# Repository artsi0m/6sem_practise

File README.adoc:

/// -*- mode: adoc; -*-
= PCB project of RS485 — RS232 converter from 6 semester practise in BSUIR =

|===
| Folder | Сontent

| kicad-rs-converter
| PCB project in KiCAD

| paper
| practise report

| SEL
| structured element list (Перечень элементов)
|===

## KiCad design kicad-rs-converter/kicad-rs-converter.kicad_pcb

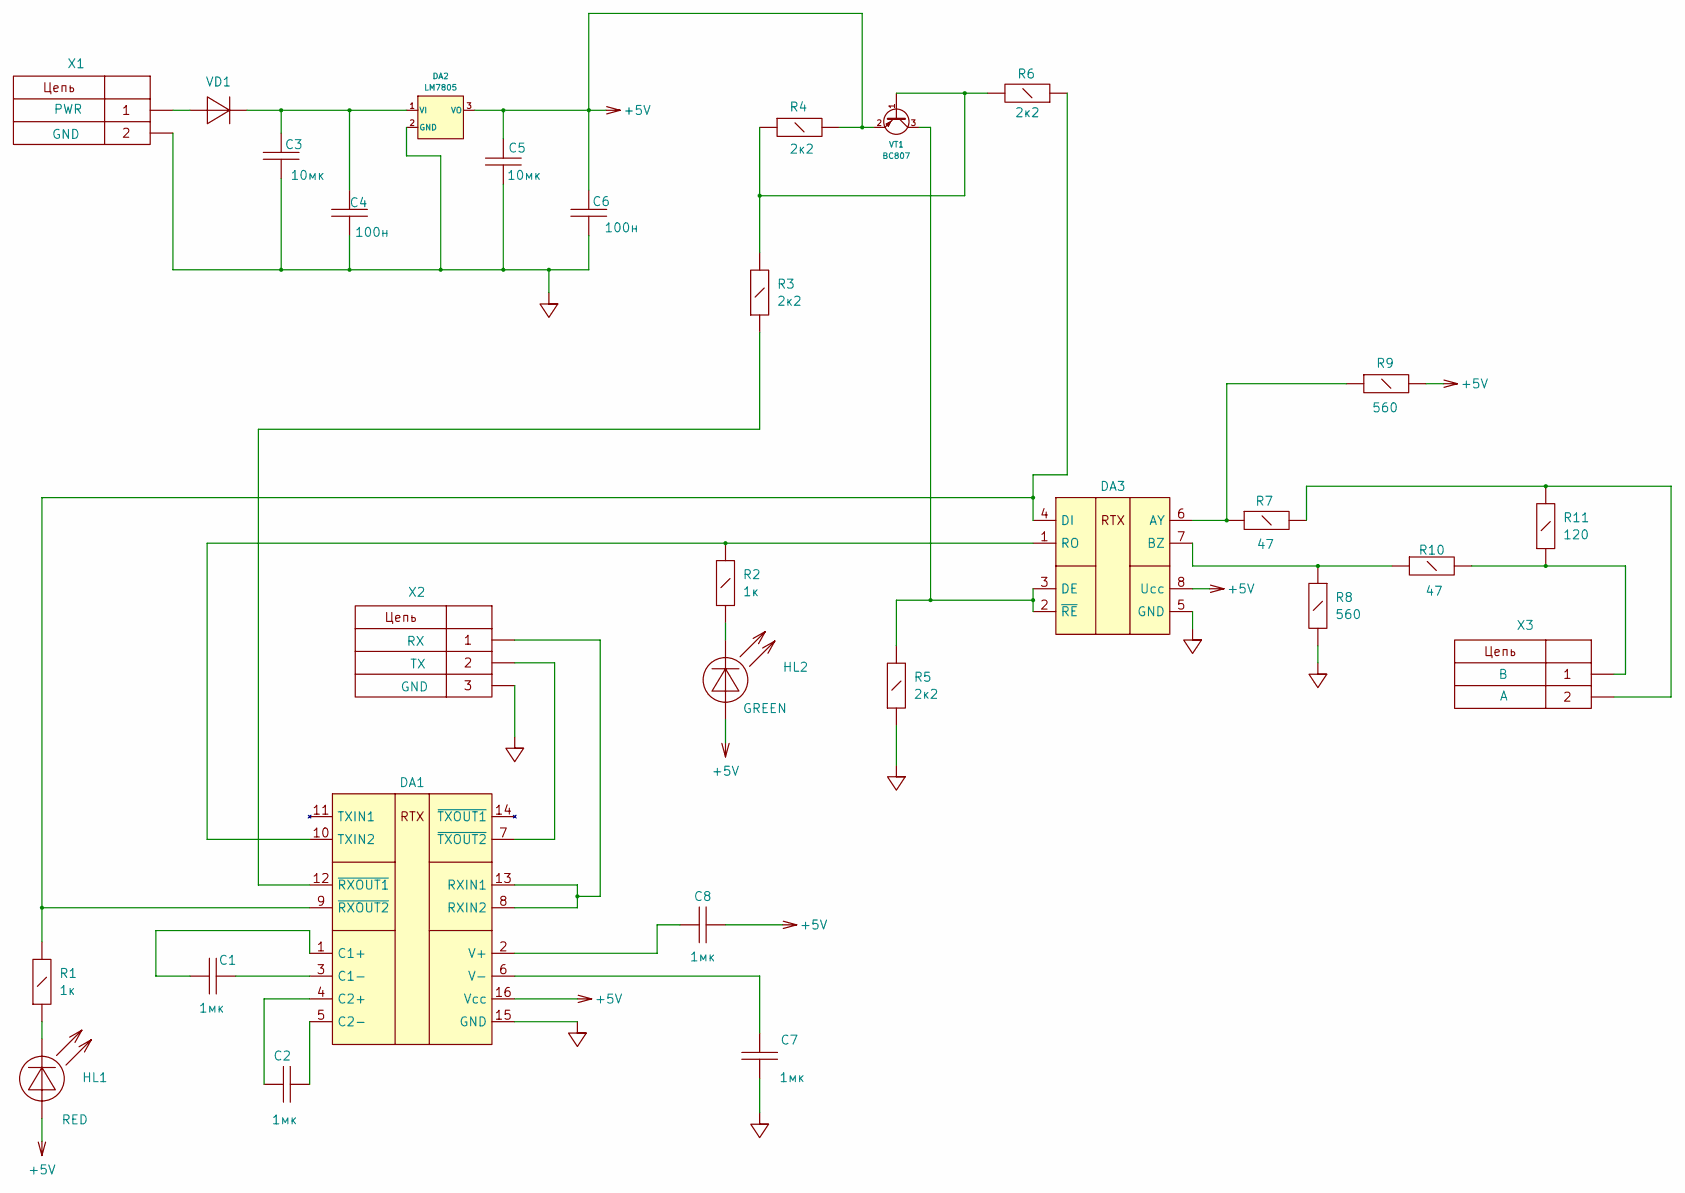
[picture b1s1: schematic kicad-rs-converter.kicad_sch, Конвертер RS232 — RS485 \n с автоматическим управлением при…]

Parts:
C1, C2, C7, C8: 1мк; C_1206_3216Metric
C3, C5: 10мк; C_1206_3216Metric
C4, C6: 100н; C_1206_3216Metric
DA1: MAX232_GOST; SO-16_3.9x9.9mm_P1.27mm
DA2: LM7805; TO-252-2
DA3: MAX485; SO-8_3.9x4.9mm_P1.27mm
HL1: RED; LED_1210_3225Metric
HL2: GREEN; LED_1210_3225Metric
R1, R2: 1к; R_0603_1608Metric
R3, R4, R5, R6: 2к2; R_0603_1608Metric
R7, R10: 47; R_0603_1608Metric
R8, R9: 560; R_0603_1608Metric
R11: 120; R_0603_1608Metric
VD1: VD; D_0805_2012Metric
VT1: BC807; SOT-23
X1: CONN_PWR; TerminalBlock_Phoenix_PT-1,5-2-5.0-H_1x02_P5.00mm_Horizontal
X2: CONN_RS232; TerminalBlock_Phoenix_PT-1,5-3-5.0-H_1x03_P5.00mm_Horizontal
X3: CONN_2; TerminalBlock_Phoenix_PT-1,5-2-5.0-H_1x02_P5.00mm_Horizontal

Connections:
+5V: C5.1, C6.1, C8.2, DA1.16 (Vcc), DA2.3 (VO), DA3.8 (Ucc), HL1.2 (A), HL2.2 (A), R4.2, R9.2, VT1.2 (E)
GND: C3.2, C4.2, C5.2, C6.2, C7.1, DA1.15 (GND), DA2.2 (GND), DA3.5 (GND), R5.1, R8.2, X1.2, X2.3
unnamed: C1.1, DA1.1 (C1+)
unnamed: C1.2, DA1.3 (C1-)
unnamed: C2.1, DA1.4 (C2+)
unnamed: C2.2, DA1.5 (C2-)
unnamed: DA1.8 (RXIN2), DA1.13 (RXIN1), X2.1
unnamed: DA1.10 (TXIN2), DA3.1 (RO), R2.2
unnamed: C8.1, DA1.2 (V+)
unnamed: C7.2, DA1.6 (V-)
unnamed: DA1.12 (~RXOUT1), R3.1
unnamed: DA1.9 (~RXOUT2), DA3.4 (DI), R1.2, R6.1
unnamed: DA1.7 (~TXOUT2), X2.2
unnamed: C3.1, C4.1, DA2.1 (VI), VD1.1 (K)
unnamed: DA3.6 (AY), R7.1, R9.1
unnamed: DA3.7 (BZ), R8.1, R10.1
unnamed: DA3.2 (~RE), DA3.3 (DE), R5.2, VT1.3 (C)
unnamed: HL1.1 (K), R1.1
unnamed: HL2.1 (K), R2.1
unnamed: R10.2, R11.1, X3.1
unnamed: R7.2, R11.2, X3.2
unnamed: VD1.2 (A), X1.1
unnamed: R3.2, R4.1, R6.2, VT1.1 (B)

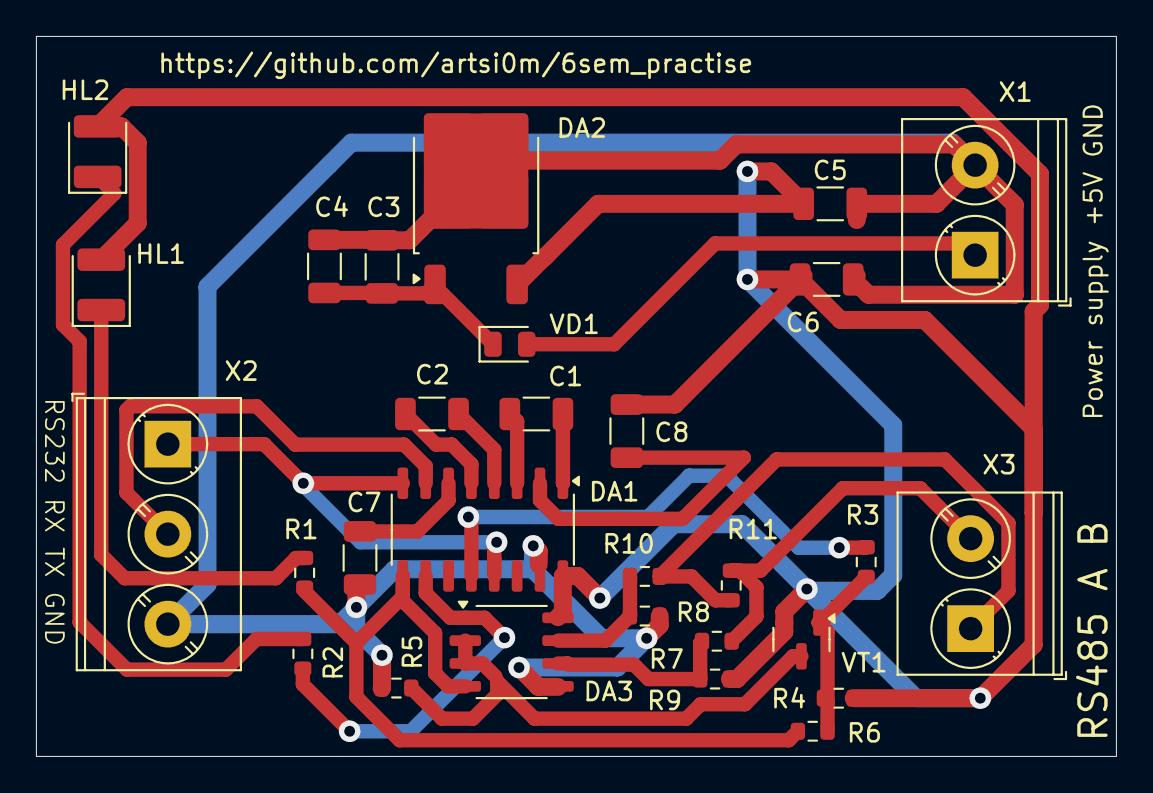
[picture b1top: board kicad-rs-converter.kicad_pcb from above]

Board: 2 copper layers, 60.0 x 40.0 mm, 29 parts (0 on the bottom side), 23 nets.

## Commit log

2024-06-11 Initiated with autogenerated gitignore file.
2024-06-11 Imported class file from 6 sem coursework repo
2024-06-11 Copied build script from repo of the coursework
2024-06-11 Excluding compilation result
2024-06-11 Added copied files from 6sem couserwork +test file + bibliography
2024-06-18 Initial commit with empty kicad project
2024-06-19 Рамка по ГОСТ
2024-06-19 Placed two XS's on scheme
2024-06-19 Created symbol library and copied MAX485CPA from GOST library
2024-06-19 Filter out kicad lock files with gitignore
2024-06-19 Filter out kicad lock files with .gitignore attempt 2
2024-06-19 Changed link to datasheet
2024-06-19 That symbol was already present in GOST library
2024-06-20 rewriting title.tex from coursework
2024-06-20 Placed MAX232 to the left as much as I could
2024-06-20 Part of the circuit with the second LED
2024-06-20 Created GOST symbol for LM7805
2024-06-20 Created part of circuit with voltage regulator
2024-06-20 Created part of circuit with MAX485 only
2024-06-20 Placed MAX485 on the scheme
2024-06-20 Schematics almost done, all parts of circuit is on the scheme
2024-06-20 Fixed scheme, pwr connector named, RXOUT2 of MAX484 connected
2024-06-20 Write down surnames
2024-06-20 Scheme annotation
2024-06-20 Placed values on every element
2024-06-20 s/LM7805_TO220_GOST/LM7805/
2024-06-20 MAX232 and MAX485 in my own library
2024-06-20 Fixing errors from ERC
2024-06-20 ERC fix with PWR_flag, PWR_CONN in sym_lib, package for MAX232 assigned
2024-06-20 BC327 to BC807 smd, SOT-23, set most of the scheme to smd.
2024-06-21 A4 to A3, because of the GOST norms for sheet
2024-06-21 Renamed designators of MAX485 and MAX232 to DA from DD
2024-06-21 Created separate connector symbol for RS232
2024-06-21 Schematic redone on A3
2024-06-21 Assigned values almost everywhere, writing sheet
2024-06-21 ESKD class assigned
2024-06-21 footprints for MAX232 & MAX485
2024-06-21 Placed footprints for LED
2024-06-21 Placed footprints for Resistors
2024-06-21 Placed footprints for polar capacitors
2024-06-21 Footprint for SMD Capacitors and Resistors
2024-06-24 Changed from polar CP capacitors to regular capacitors C
2024-06-24 Assigned footprint of SMD:C_1206_3216 Metric to every capacitor
2024-06-24 Assigned footprints for X connector — Terminal Block
2024-06-24 Imported footprints from schematics into PCB layout
2024-06-24 Assigned netclasses and colors for cicuits
2024-06-24 Drawing edge cuts
2024-06-24 PCBdoc: everything connected except for GND and +5V
2024-06-24 pcbdoc finished, but some parts can be done better.
2024-06-24 Made PCB layout on 70x40mm board
2024-06-24 Moved transistor BC807 and redone PCB layout a little bit.
2024-06-24 Rebuild from scratch. 0.8 track_width and 60x40mm board
2024-06-25 Exported bom
2024-06-25 Начал перечень писать
2024-06-25 More resistors
2024-06-25 README with kicad-rc-converter, paper, SEL folders mentioned
2024-06-25 quick fix to hide emacs mode directive
2024-06-25 README in org mode with 3 folders mentioned
2024-06-28 Silkscreen added on pcb
2024-06-28 Link to original schematic + formatted
2024-06-28 Full structured element list, but something with formatting
2024-07-01 Fixed DRC error from silkscreen plaeced near footprint
2024-07-01 Repaired document by removing \XeselEntry{}{}{}{} from first lines
2024-07-01 longer DocumentName, SEL seems to be fineshed
2024-07-06 There is an error, PWR_FLAG removed to see if fixing would fix ERC
2024-07-06 The fix consisted of flipping transistor
2024-07-07 trying to make place with error more readable
2024-07-07 transistor flip and reconnect on pcbdoc
2024-07-08 Fix the Surname of the one who checks the work
2024-09-02 Cannot build on openSUSE, no such font in fetchmsttfonts
2024-09-02 Building this paper on openSUSE instead of windows
2024-09-02 installed opengost-ttf-fonts on my laptop
2024-09-02 xesel class from Danil Gulin repo, changed color to black
2024-09-02 Move away from eskdx class
2024-09-02 СТП part into class, comments and separation in sections
2024-09-02 paragraph ident
2024-09-02 Doing TOC instead of title
2024-09-03 sections
2024-09-03 properly done labels
2024-09-03 Rotkop1976 from 5sem
2024-09-03 no more emptystyle from eskdx
2024-09-03 Starting to write
2024-09-05 surname fix
2024-09-05 seems to be almost full
2024-09-05 fix title hyphenation
2024-09-05 some more bits for first part
2024-09-05 some more bits for second part
2024-09-05 some more bits for fifth part
2024-09-06 More websites in sources
2024-09-06 extreport class to use pt14 font
2024-09-06 Листы по СТП, флоаты (картинки, таблицы) по номерам глав.
2024-09-06 ГОСТ принципиальных схем и перечней
2024-09-06 directories for screenshots and schematics
2024-09-06 Лист заключения
2024-09-06 faster compilation with bibliography
2024-09-06 screenshots and schematics
2024-09-06 Wrote some more
2024-09-06 quick bibliography fix
2024-09-06 another quick bibliography fix
2024-09-06 Строчка [Электронный ресурс]. Вне библиографии.
2024-09-06 trying to improve hyphention
2024-09-06 toc with intoduction and conslusion without numbers
2024-09-06 Защитил практику на 8.
2024-09-06 Номера в нумерованных списках по СТП
2024-09-09 actual date
2024-12-29 Latest version of latex class for BSUIR papers
2024-12-29 CERN Open Hardware Licence Version 2 - Permissive
2025-02-28 was asked to rebuild paper: two illustrations lost
